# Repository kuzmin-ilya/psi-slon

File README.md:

# psi-SLON electrical circuit

psi-SLON is small laboratory electrostimulator.  
This project is a part of [x-SLON project](https://github.com/comcon1/x-SLON).  
Please address the maternal project for detailed description.

Device is very small and is assembled simply. Please consult [assembly.txt](case/assembly.txt).

**Scheme of the device output**

__\*__ - reserve pin connected to ADC0 pin of the ATMEGA (100 kOhm).

# Authors

Ilya Kuzmin <kuzmin.ilya@gmail.com>  
Peter Mamonov <pmamonov@gmail.com>  
Alexey Nesterenko <comcon1@protonmail.com>  

# Licensing

"psi-SLON electrical circuit" project (I. Kuzmin, P. Mamonov, A. Nesterenko)
is released under license CC BY-SA 3.0.

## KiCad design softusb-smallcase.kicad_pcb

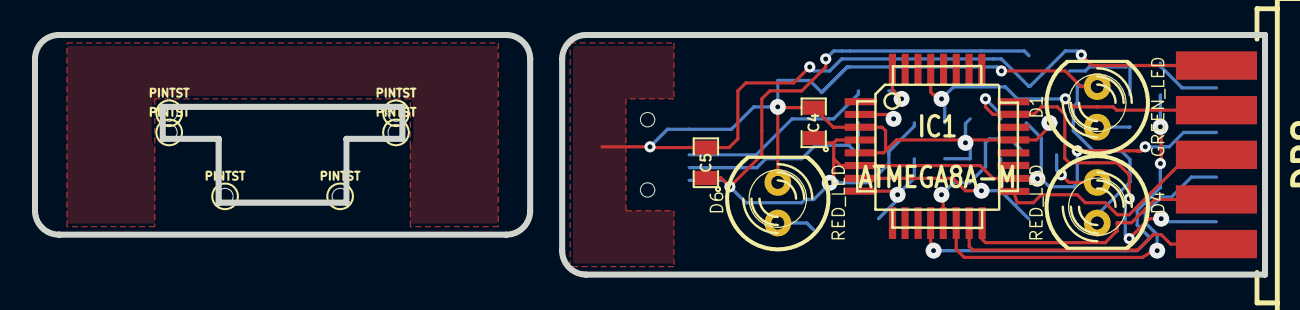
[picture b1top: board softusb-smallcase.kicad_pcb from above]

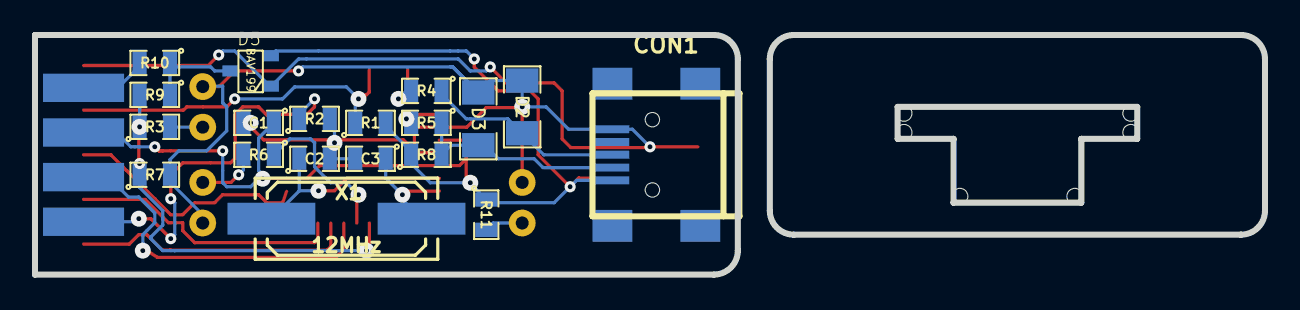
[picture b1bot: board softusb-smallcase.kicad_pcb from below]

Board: 2 copper layers, 77.0 x 15.0 mm, 32 parts (19 on the bottom side), 22 nets.

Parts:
C1, C4, C5: 0,1; SM0805
C2, C3: 22; SM0805
CON1: USB-MINI-B; USB_MINI_B
D1: GREEN_LED; LED-5MM
D2, D3: 3,3V; SM1206
D4, D6: RED_LED; LED-5MM
D5: BAV199; SOT23
IC1: ATMEGA8A-M; TQFP32
J2: DB9; DB9F_CI
PINTST: Val*; PINTST
PINTST#2, PINTST#3, PINTST#4, PINTST#5, PINTST#6: Val*; PINTST
R1, R7: 5,1k; SM0805
R2: 100k; SM0805
R3, R6, R11: 510; SM0805
R4, R5: 68; SM0805
R8, R9, R10: 1,5k; SM0805
X1: 12MHz; Q_49U3HMS

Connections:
+5V: C1.1, C4.1, C5.1, CON1.1, D5.2, IC1.4, IC1.6, IC1.18, J2.7, R1.2, R8.1, R11.1
GND: C1.2, C2.2, C3.2, C4.2, C5.2, CON1.5, D1.2, D2.1, D3.1, D4.2, D5.1, D6.2, IC1.3, IC1.5, IC1.21, J2.1, R2.2, R7.2
unnamed: C2.1, IC1.7, X1.1
unnamed: C3.1, IC1.8, X1.2
unnamed: J2.6, R10.2
unnamed: D1.1, R3.2
unnamed: D5.3, R9.1, R10.1
unnamed: CON1.3, D2.2, R4.1
unnamed: IC1.16, J2.4
unnamed: IC1.14, J2.8
unnamed: IC1.2, R5.2
unnamed: IC1.15, J2.5
unnamed: IC1.32, R4.2
unnamed: CON1.2, D3.2, R5.1, R8.2
unnamed: IC1.17, J2.3
unnamed: D6.1, R11.2
unnamed: IC1.12, R3.1, R7.1, R9.2
unnamed: IC1.23, J2.9, R2.1
unnamed: IC1.13, R6.1
unnamed: D4.1, R6.2
unnamed: IC1.29, J2.2, R1.1
unnamed: PINTST#2.1, PINTST#3.1, PINTST#4.1, PINTST#5.1, PINTST#6.1

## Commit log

2018-10-11 moving to git
2018-10-22 Removing backup files
2018-10-22 Case files are confirmed.
2018-10-22 Adding README and LICENSE.
2018-10-27 Adding OUTPUT SHEME to README.
